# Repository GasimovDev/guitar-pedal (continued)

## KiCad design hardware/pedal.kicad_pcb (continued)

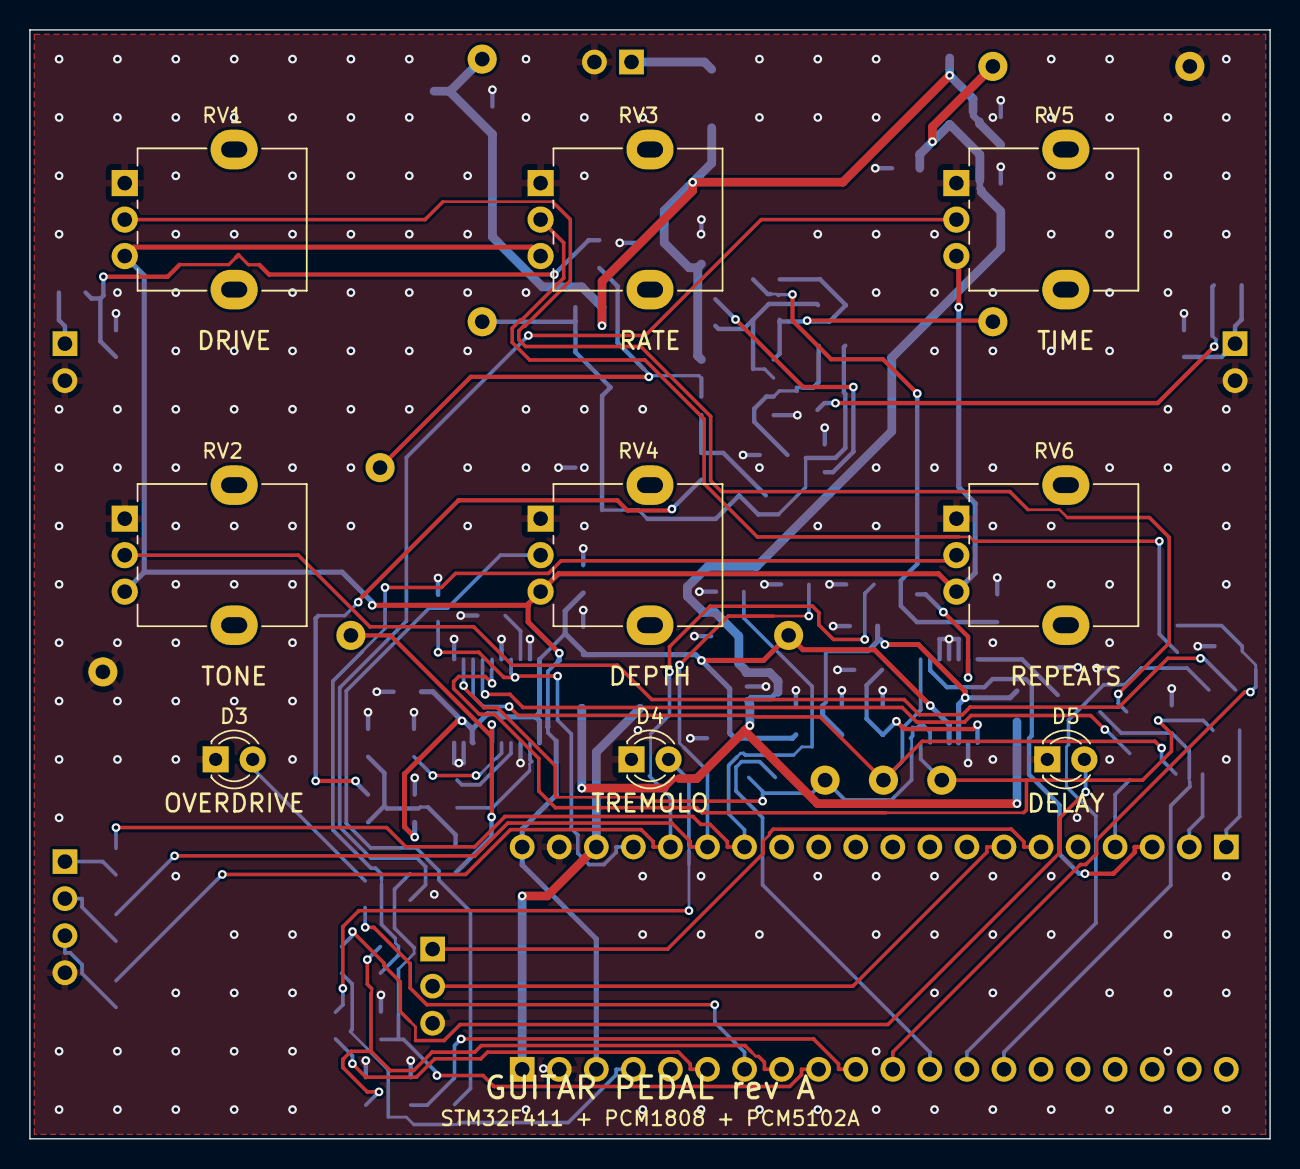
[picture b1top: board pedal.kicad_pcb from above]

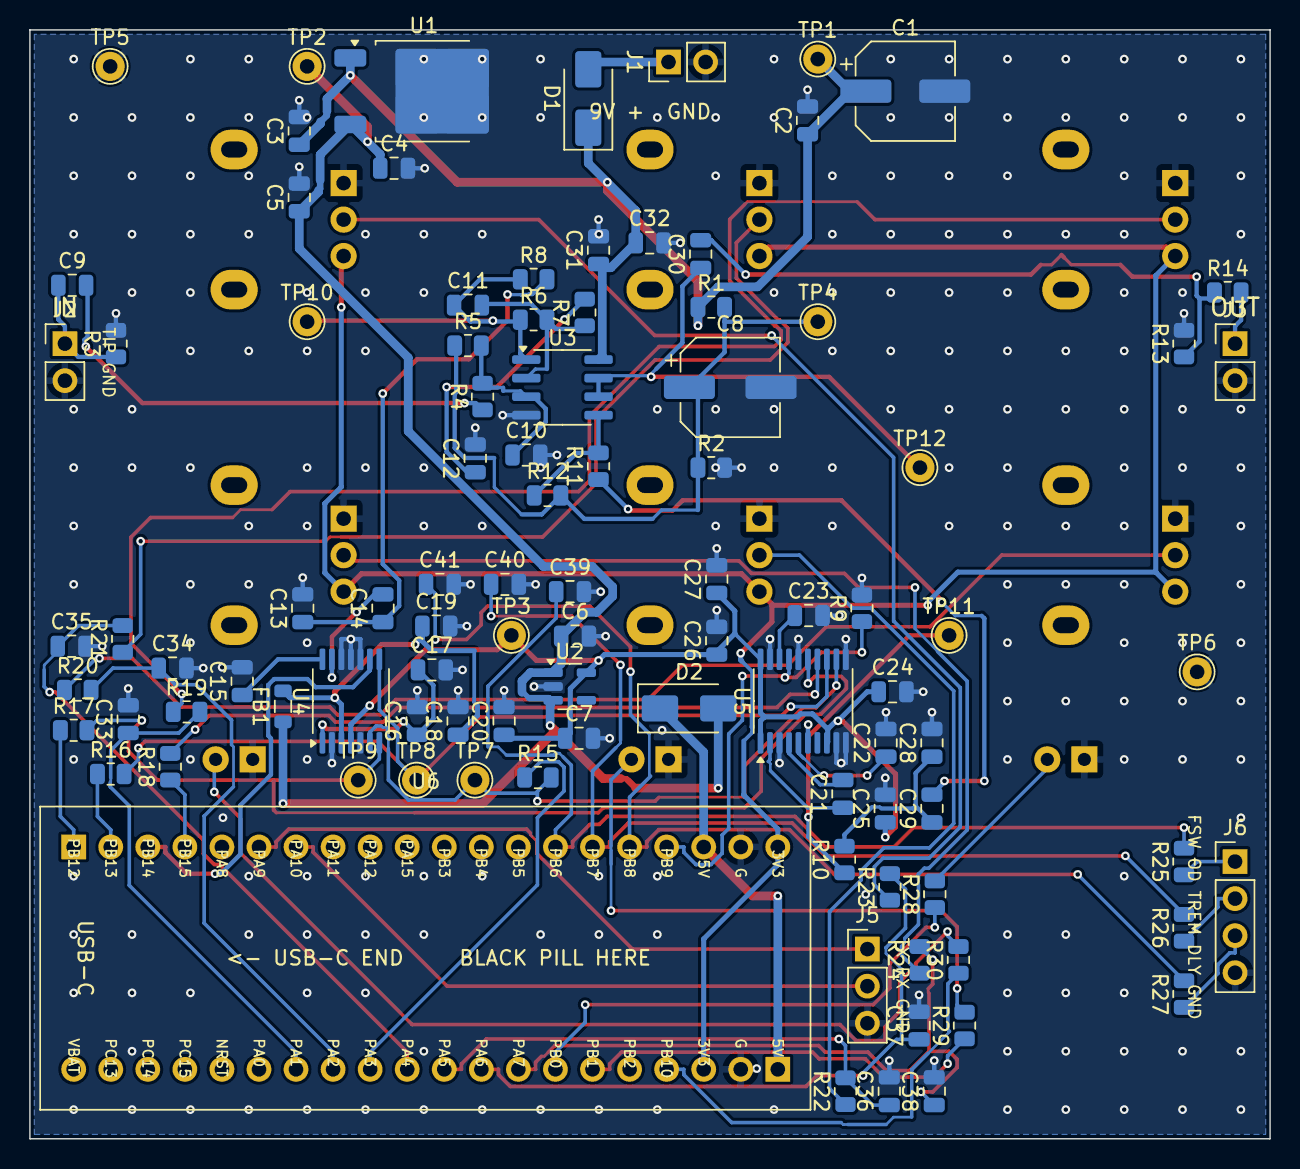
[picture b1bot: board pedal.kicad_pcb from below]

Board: 2 copper layers, 85.0 x 76.0 mm, 106 parts (97 on the bottom side), 66 nets.

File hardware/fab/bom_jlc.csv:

Comment,Designator,Footprint,LCSC Part #,Manufacturer Part,Qty
100uF 25V electrolytic,C1,SMD electrolytic 6.3x7.7mm,,,1
100nF 50V X7R/X5R,"C2,C5,C9,C17,C19,C20,C25,C26,C27,C31,C33,C34,C35,C36,C37,C38,C39,C40,C41",0805,,,19
1uF 25V X7R/X5R,C3,0805,,,1
10uF 16V X7R/X5R,"C4,C7,C12,C14,C16,C18,C24,C29,C30",0805,,,9
1uF 16V X7R/X5R,"C6,C15,C23",0805,,,3
47uF 25V electrolytic,C8,SMD electrolytic 6.3x5.4mm,,,1
100pF 50V C0G/NP0,"C10,C11",0805,,,2
2.2nF 50V C0G/NP0,"C13,C28",0805,,,2
2.2uF 16V X7R/X5R,"C21,C22",0805,,,2
10uF 25V X7R/X5R,C32,0805,,,1
SS34,D1,SMA (DO-214AC),,SS34,1
SS14,D2,SMA (DO-214AC),,SS14,1
Ferrite bead 600R@100MHz,FB1,0805,,BLM21PG601SN1D,1
10k 1% 1/8W,"R1,R2,R7,R9,R12",0805,,,5
1M 1% 1/8W,"R3,R5",0805,,,2
1k 1% 1/8W,"R4,R8,R14,R19,R20,R21,R22,R23,R24,R25,R26,R27",0805,,,12
5.1k 1% 1/8W,R6,0805,,,1
470 1% 1/8W,"R10,R28,R29,R30",0805,,,4
22k 1% 1/8W,R11,0805,,,1
100k 1% 1/8W,R13,0805,,,1
33 1% 1/8W,"R15,R16,R17,R18",0805,,,4
L78M05,U1,TO-252 (DPAK),,L78M05CDT-TR,1
AP2112K-3.3,U2,SOT-23-5,,AP2112K-3.3TRG1,1
OPA1678,U3,SOIC-8,,OPA1678IDR,1
PCM1808,U4,TSSOP-14,,PCM1808PWR,1
PCM5102A,U5,TSSOP-20,,PCM5102APWR,1

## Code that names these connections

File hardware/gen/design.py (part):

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BP_B = ["PB12", "PB13", "PB14", "PB15", "PA8", "PA9", "PA10", "PA11", "PA12", "PA15", "PB3", "PB4", "PB5",
        "PB6", "PB7", "PB8", "PB9", "5V", "GND", "3V3"]
bp_net = {"5V": "+5V_MCU", "GND": "GND", "3V3": "+3V3_MCU",
          "PB10": "LED3", "PB1": "LED2", "PB0": "LED1",
          "PA7": "K6", "PA6": "K5", "PA5": "K4", "PA4": "K3", "PA2": "K2", "PA1": "K1",
          "PA3": "MCU_MCLK", "PB12": "MCU_LRCK", "PB13": "MCU_BCK", "PB14": "ADC_DOUT", "PB15": "MCU_DIN",
          "PA9": "UART_TX", "PA10": "UART_RX", "PB6": "FSW1", "PB7": "FSW2", "PB8": "FSW3", "PB9": "DAC_XSMT"}
bp_pins = {}
for i, n in enumerate(BP_A):
    bp_pins[str(i + 1)] = bp_net.get(n)
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
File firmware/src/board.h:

/*
 * board.h - which STM32 pin is wired to what on the pedal PCB.
 * Must match hardware/ (schematic net names in brackets).
 *
 *  Audio (I2S2, full duplex)
 *    PA3  I2S2_MCK   AF5  -> PCM1808 SCKI, PCM5102A SCK   [MCLK]  12.29 MHz
 *    PB13 I2S2_CK    AF5  -> both converters' BCK          [BCK]    3.07 MHz
 *    PB12 I2S2_WS    AF5  -> both converters' LRCK         [LRCK]  48 kHz
 *    PB15 I2S2_SD    AF5  -> PCM5102A DIN  (DAC data out)  [DAC_DIN]
 *    PB14 I2S2ext_SD AF6  <- PCM1808 DOUT  (ADC data in)   [ADC_DOUT]
 *    PB9  GPIO out        -> PCM5102A XSMT (low = mute)    [DAC_XSMT]
 *
 *  Knobs (ADC1, 0..3.3 V, ratiometric)
 *    PA1 IN1 DRIVE   PA2 IN2 TONE   PA4 IN4 RATE
 *    PA5 IN5 DEPTH   PA6 IN6 TIME   PA7 IN7 REPEATS
 *
 *  Footswitches (to GND when pressed, internal pull-up)
 *    PB6 OD   PB7 TREM   PB8 DELAY
 *
 *  LEDs (high = on)
 *    PB0 OD   PB1 TREM   PB10 DELAY       PC13 = Black Pill's own LED (low = on)
 *
 *  Debug UART (USART1, 115200 8N1)
 *    PA9 TX   PA10 RX
 */
#ifndef BOARD_H
#define BOARD_H

#include "stm32f4xx.h"

#define SYSCLK_HZ   96000000u
#define APB1_HZ     48000000u
#define APB2_HZ     96000000u

/* Exact rate the I2S clock tree gives: 86 MHz / (256 * 7) */
#define AUDIO_FS_HZ 47991.07f

/* Half of the DMA buffer is processed at a time: 32 frames = 0.67 ms. */
#define AUDIO_BLOCK 32

/* Small helpers for GPIO setup. mode: 0 in, 1 out, 2 alternate, 3 analog */
static inline void gpio_mode(GPIO_TypeDef *g, int pin, int mode)
{
    g->MODER = (g->MODER & ~(3u << (pin * 2))) | ((uint32_t)mode << (pin * 2));
}
static inline void gpio_af(GPIO_TypeDef *g, int pin, int af)
{
    volatile uint32_t *r = &g->AFR[pin >> 3];
    int s = (pin & 7) * 4;
    *r = (*r & ~(0xFu << s)) | ((uint32_t)af << s);
    gpio_mode(g, pin, 2);
}
static inline void gpio_speed_high(GPIO_TypeDef *g, int pin)
{
    g->OSPEEDR |= (3u << (pin * 2));
}
static inline void gpio_pullup(GPIO_TypeDef *g, int pin)
{
    g->PUPDR = (g->PUPDR & ~(3u << (pin * 2))) | (1u << (pin * 2));
}
static inline void gpio_write(GPIO_TypeDef *g, int pin, int on)
{
    g->BSRR = on ? (1u << pin) : (1u << (pin + 16));
}
static inline int gpio_read(GPIO_TypeDef *g, int pin)
{
    return (g->IDR >> pin) & 1u;
}

#endif
